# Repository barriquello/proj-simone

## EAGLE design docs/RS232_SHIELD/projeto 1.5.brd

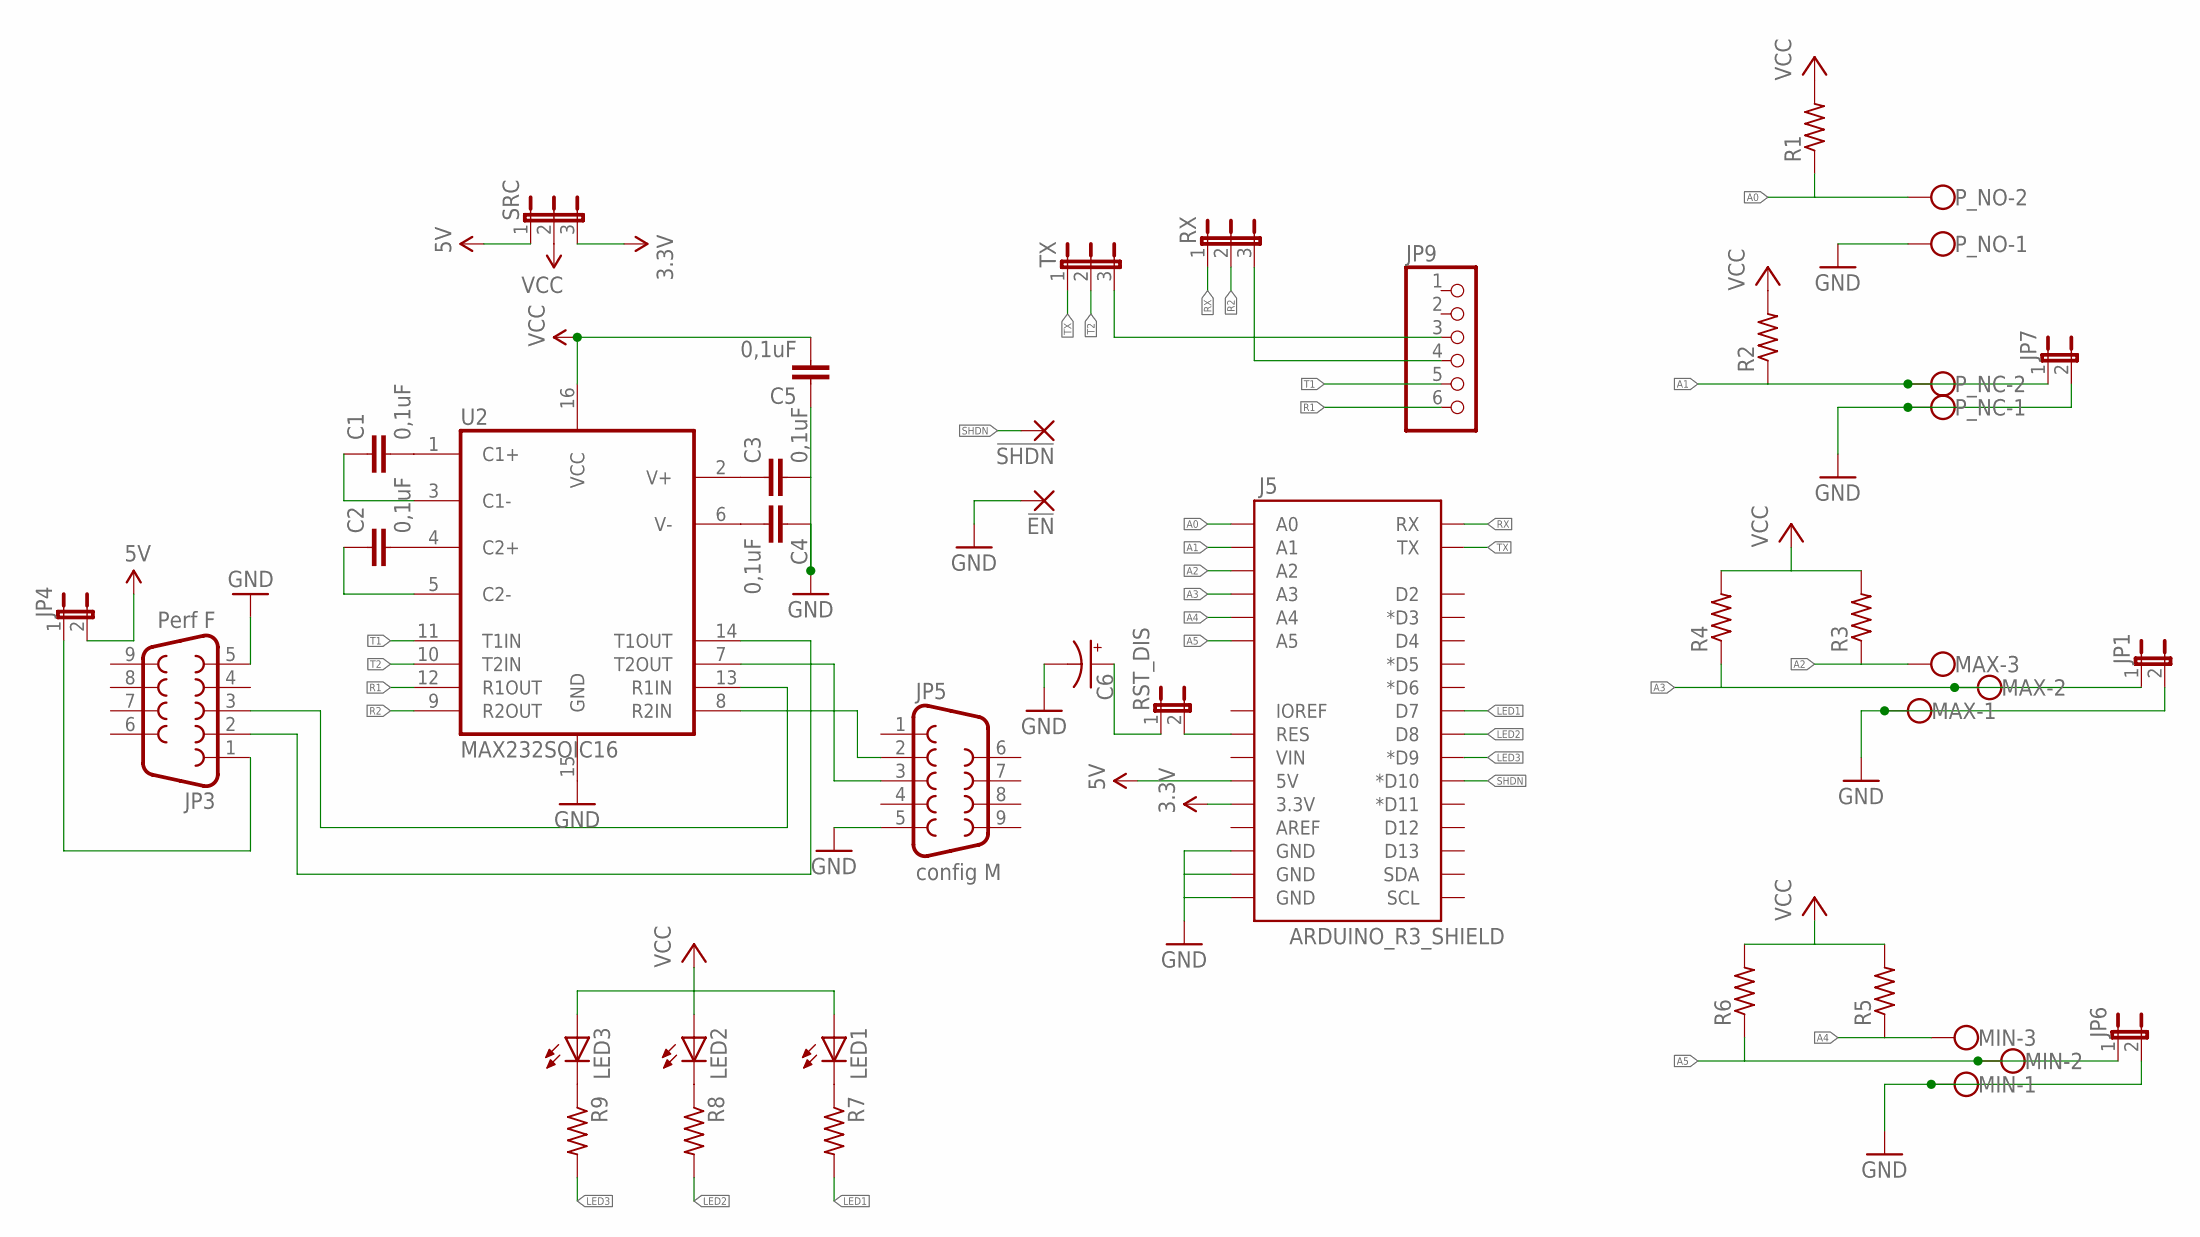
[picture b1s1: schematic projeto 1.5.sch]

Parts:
!EN: SMD2; SMD1,27-2,54
!SHDN: SMD2; SMD1,27-2,54
C1, C2, C3, C4, C5: 0,1uF; C0805K
C6: CPOL-USTT5D10; TT5D10
J5: ARDUINO_R3_SHIELD; UNO_R3_SHIELD
JP1, JP4, JP6, JP7: JP1E; JP1
JP3: Perf F; DB9
JP5: config M; DB9_MALE
JP9: PINHD-1X6; 1X06
LED1, LED2, LED3: LED3MM
MAX: W237-103
MIN: W237-103
P_NC: W237-102
P_NO: W237-102
R1, R2, R3, R4, R5, R6, R7, R8, R9: R-US_R0805; R0805
RST_DIS: JP1E; JP1
RX: JP2W
SRC: JP2W
TX: JP2W
U2: MAX232SOIC16; SO016

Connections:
3.3V: J5.3.3V, SRC.3
5V: J5.5V, JP4.2, SRC.1
A0: J5.A0, P_NO.2, R1.1
A1: J5.A1, JP7.1, P_NC.2, R2.1
A2: J5.A2, MAX.3, R3.1
A3: J5.A3, JP1.1, MAX.2, R4.1
A4: J5.A4, MIN.3, R5.1
A5: J5.A5, JP6.1, MIN.2, R6.1
GND: !EN.1, C3.2, C4.1, C5.1, C6.-, J5.GND@0 (GND), J5.GND@1 (GND), J5.GND@2 (GND), JP1.2, JP3.5, JP5.5, JP6.2, JP7.2, MAX.1, MIN.1, P_NC.1, P_NO.1, U2.15 (GND)
LED1: J5.D7, R7.2
LED2: J5.D8, R8.2
LED3: J5.D9 (*D9), R9.2
unnamed: LED1.K (C), R7.1
unnamed: C1.2, U2.1 (C1+)
unnamed: JP9.4, RX.3
unnamed: C2.2, U2.4 (C2+)
unnamed: C1.1, U2.3 (C1-)
unnamed: LED2.K (C), R8.1
unnamed: C2.1, U2.5 (C2-)
unnamed: JP9.3, TX.3
unnamed: J5.RES, RST_DIS.2
unnamed: C6.+, RST_DIS.1
unnamed: JP5.3, U2.7 (T2OUT)
unnamed: LED3.K (C), R9.1
unnamed: C3.1, U2.2 (V+)
unnamed: JP5.2, U2.8 (R2IN)
unnamed: JP3.3, U2.13 (R1IN)
unnamed: JP3.1, JP4.1
unnamed: JP3.2, U2.14 (T1OUT)
unnamed: C4.2, U2.6 (V-)
R1: JP9.6, U2.12 (R1OUT)
R2: RX.2, U2.9 (R2OUT)
RX: J5.RX, RX.1
SHDN: !SHDN.1, J5.D10 (*D10)
T1: JP9.5, U2.11 (T1IN)
T2: TX.2, U2.10 (T2IN)
TX: J5.TX, TX.1
VCC: C5.2, LED1.A, LED2.A, LED3.A, R1.2, R2.2, R3.2, R4.2, R5.2, R6.2, SRC.2, U2.16 (VCC)

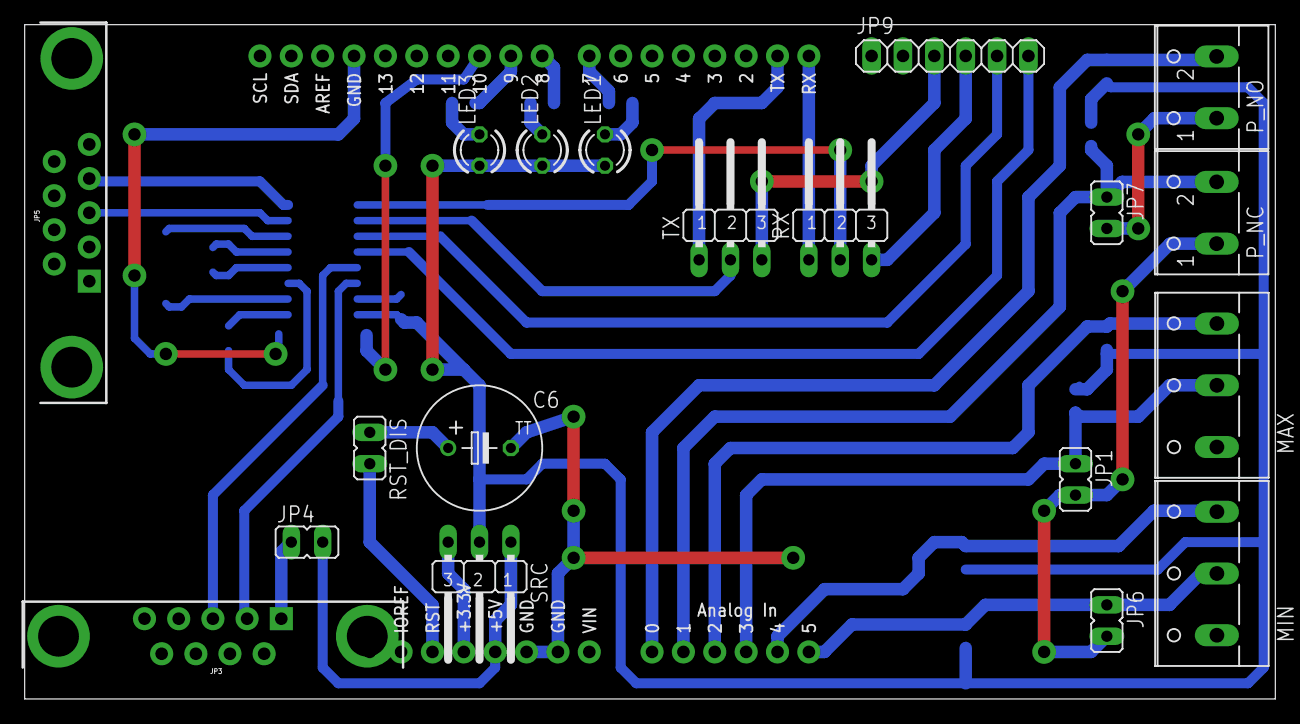
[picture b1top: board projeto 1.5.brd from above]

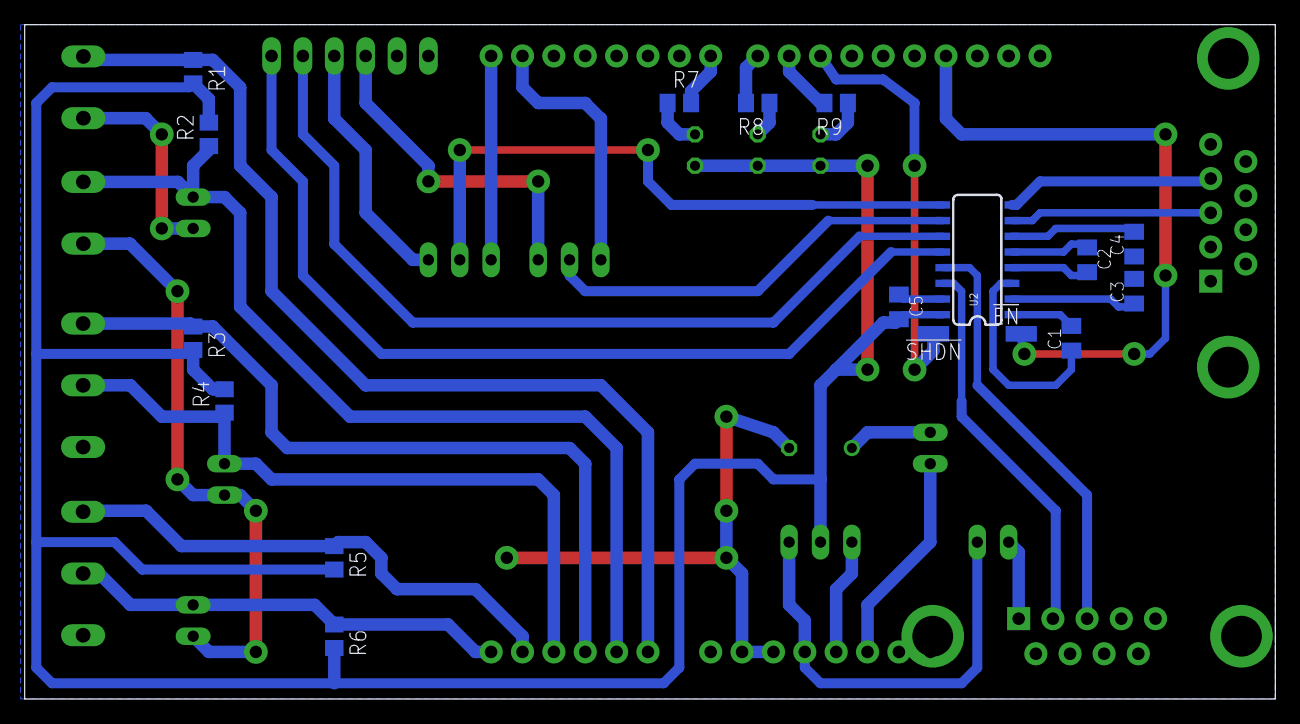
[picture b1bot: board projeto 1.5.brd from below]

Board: 2 copper layers, 101.3 x 54.6 mm, 37 parts (17 on the bottom side), 38 nets.

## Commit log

2015-06-27 demo brtos atmega328p
2015-06-27 hal atmega328p
2015-06-28 demos: atmega2650 e atmega328p
2015-06-28 demos: atmega256 e atmega328p
2015-06-29 ATMEGA port for Atmel Studio
2015-06-29 arduino-simone
2015-06-29 colduino-simone
2015-07-01 included devices folder
2015-07-01 folder and files organization
2015-07-02 simone-arduino
2015-07-02 devices
2015-07-02 updated main_app
2015-07-02 arduino mcu driver
2015-07-03 docs do projeto - estrutura do projeto e lógica da tarefa monitor
2015-07-04 devices organization
2015-07-04 timer_lib e logger (monitor)
2015-07-17 logger task
2015-07-22 added simon-api e terminal-io
2015-07-23 updated win32 version
2015-07-23 check configuration
2015-07-28 agenda do projeto
2015-07-28 adição de licença
2015-08-07 fix in terminal stdout (USB = 0, UART1 = 1, UART2 = 2)
2015-08-07 colduino docs
2015-08-10 m590 driver
2015-08-10 m590 http works
2015-08-11 m590 http working
2015-08-11 added terminal app
2015-08-12 random lib
2015-08-12 limpeza e melhorias no codigo
2015-08-13 fatfs reentrant
2015-08-14 win32 compilando
2015-08-14 modbus slaves
2015-08-15 codigo menor
2015-08-16 otimizacoes de codigo
2015-08-16 mais otimizacoes
2015-08-17 rs485 driver corrigido
2015-08-17 testando monitor com SD
2015-08-18 monitor write quase escrevendo header, mas falta linha com dados
2015-08-18 monitor write ok
2015-08-19 monitor writer ok
2015-08-20 modem driver
2015-08-20 http win driver
2015-08-21 m590 driver nao funcionando
2015-08-22 simon get time ok
2015-08-23 simon api
2015-08-23 simon send ok
2015-08-25 change in win32 port
2015-08-27 add http client
2015-09-02 uploading to emoncms ok
2015-09-03 port para Arduino
2015-09-04 bug fix = modem m590, send
2015-09-09 m590 get time at command
2015-09-11 modbus terminal command
2015-09-13 win32 port bug fix
2015-09-16 modbus master bug fix, modbus t500 driver
2015-09-18 otimizações
2015-09-18 stats
2015-09-18 improved modem driver
2015-09-21 adição da licença
2015-09-21 bug fix: debug stack
2015-09-22 removed freemodbus
2015-09-28 diversas otimizações e correções
2015-10-01 issue: modbus t500 resetting
2015-10-01 port for CFv1 GCC
2015-10-05 ported to Colduino GCC
2015-10-16 port to GCC
2015-10-18 arduino port
2015-10-19 cfv1 gcc port bug fix
2015-10-20 port to arduino mega 2560
2015-10-21 compilando para Arduino
2015-10-22 compilando para atmega2560
2015-10-23 port to arduino mega2560
2015-10-24 bug fix - printP_uart2
2015-10-25 strings to ROM no arduino
2015-10-25 strings in ROM for arduino
2015-10-26 cmds ver, top ok
2015-10-28 arduino port. Bug fix - top cmd
2015-10-28 arduino port - ls cmd not working
2015-10-29 change in arduino project
2015-10-29 printf_lib %l format added for long int
2015-10-29 top cmd working - arduino
2015-10-29 arduino console cmds ok
2015-10-31 ajuste dos tamanhos das pilhas para arduino
2015-10-31 added null modem driver
2015-10-31 change in sd_api, memory optimization
2015-11-01 cmd cat ok
2015-11-02 use less data mem
2015-11-03 compilando monitor no arduino
2015-11-05 ajustes p/ cfv1
2015-11-05 simulation on arduino
2015-11-05 port para Atmel Studio 7
2015-11-06 prints_erro added
2015-11-06 changing print functions
2015-11-08 travando monitor 1
2015-11-09 modbus ok
2015-11-10 arduino terminal+modbus ok
2015-11-11 terminal no arduino - rs485 e console juntos
2015-11-13 terminal - cmd mb ok
2015-11-16 alterado strcmp to strcmp_P e modbus pm210 slave
2015-11-17 cmd modbus read device
2015-11-18 cmd modbus read device regs ok
2015-11-24 driver gc864 modem
2015-11-30 colduino GCC compilando
2015-12-01 GCC colduino port working fine
2015-12-03 gc864 driver ok, monitor status cmd ok
2015-12-04 adicionado verbose level
2015-12-04 fix for arduino compilation
2015-12-08 update for arduino
2015-12-11 small fixes. TODO: check localtime function
2015-12-13 time lib bug fix for arduino
2015-12-13 bug fix time_lib for arduino
2015-12-14 arduino working - need improvements for log synch
2015-12-15 fix for little endian
2015-12-16 added doxygen travis script
2015-12-16 change doxygen erros count
2015-12-16 adicionados comandos mon time and mon list
2015-12-18 added mon time, mon list commands
2015-12-22 bug fix - index calculation for monitor read entry
2015-12-22 change mon k cmd - synch time
2015-12-28 enable echo cmd
2015-12-28 add at cmds ref. guide
2015-12-28 try to force modem reset after too many errors
2015-12-29 add command for mcu_reset
2015-12-29 modem close connection after max errors and try a new connection
2016-01-10 add modem server config
2016-01-12 updated modbus TS slave
2016-01-13 improved debug
2016-01-13 adicionada troca de arquivo cheio.
2016-01-14 modbus null reading real inputs
2016-01-15 improved gc864 driver
2016-01-18 driver gc864, adicionado dns resolver, faltando teste com IP direto e cancelamento de conexao
2016-01-19 driver gc864 aparentemente estavel
2016-01-19 hack to mix monitors data
2016-01-20 added simon_send_data_multiple to send all monitors at one time
2016-01-25 include sensors driver
2016-01-30 improved sensors driver
2016-02-01 bug fix; unix time calculation
2016-02-11 adicionado projeto shield
2016-02-12 update sensors and modbus null slave
2016-02-13 bug fix; sensors read; pull up when open
2016-02-17 add tools and mk files
2016-02-17 updating to new shield
2016-02-18 verifying sensors connection
2016-02-22 adicionado relatorio
2016-02-22 revisao do relatorio
2016-02-22 relatorio atualizado
2016-02-24 atualização do relatório
2016-02-27 updating led_onboard
2016-02-27 adição de apresentação ppt
2016-02-27 optimizing and fix led_onboard_state
2016-02-28 add script for feed testing
2016-02-29 add LED signals
2016-02-29 bug fix; led_onboard not initializing
2016-03-01 atualização do relatório e apresentação
2016-03-02 atualização de relatório e apresentação
2016-03-03 atualização da apresentação
2016-03-04 adicionado "treinamento.ppt"
2016-03-04 atualização de relatório e treinamento
2016-03-04 atualização de treinamento
2016-03-04 atualiza scripts
2016-03-04 atualização de relatório
2016-03-05 adição do grupo Devices p/ documentação doxygen
2016-03-05 organização em grupos para doxygen
2016-03-05 atualização doxygen
2016-03-05 add doxygen config file
2016-03-05 add refman
2016-03-05 alteração em refman
2016-03-05 Atualizacao relatorio
2016-03-06 updating eagle files
2016-03-06 adding gerbers
2016-03-06 Atualização relatório
2016-03-06 change doxygen error cnt to pass travis
2016-03-07 atualização da apresentação de treinamento
2016-03-07 atualiza comentarios para doxygen
2016-03-08 atualiza doxygen
2016-03-08 atualização do doxygen
2016-03-10 fix setup of feeds
2016-03-10 fix doxygen doc
2016-03-11 remove include inexistente
2016-03-12 atualização do relatório - versão de entrega
2016-03-13 atualiza projeto p/ atmel studio 6.2

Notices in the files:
parts and their libraries:
SparkFun-Boards: Licensing: Creative Commons ShareAlike 4.0 International - https://creativecommons.org/licenses/by-sa/4.0
